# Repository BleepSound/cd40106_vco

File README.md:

[![CC BY-SA 4.0][cc-by-sa-shield]][cc-by-sa]

# CD40106 VCO

Latest documentation available at https://bleepsound.github.io/modules/

[![CC BY-SA 4.0][cc-by-sa-image]][cc-by-sa]

[cc-by-sa]: http://creativecommons.org/licenses/by-sa/4.0/
[cc-by-sa-image]: https://licensebuttons.net/l/by-sa/4.0/88x31.png
[cc-by-sa-shield]: https://img.shields.io/badge/License-CC%20BY--SA%204.0-lightgrey.svg

[![CC BY-SA 4.0][cc-by-sa-shield]][cc-by-sa]

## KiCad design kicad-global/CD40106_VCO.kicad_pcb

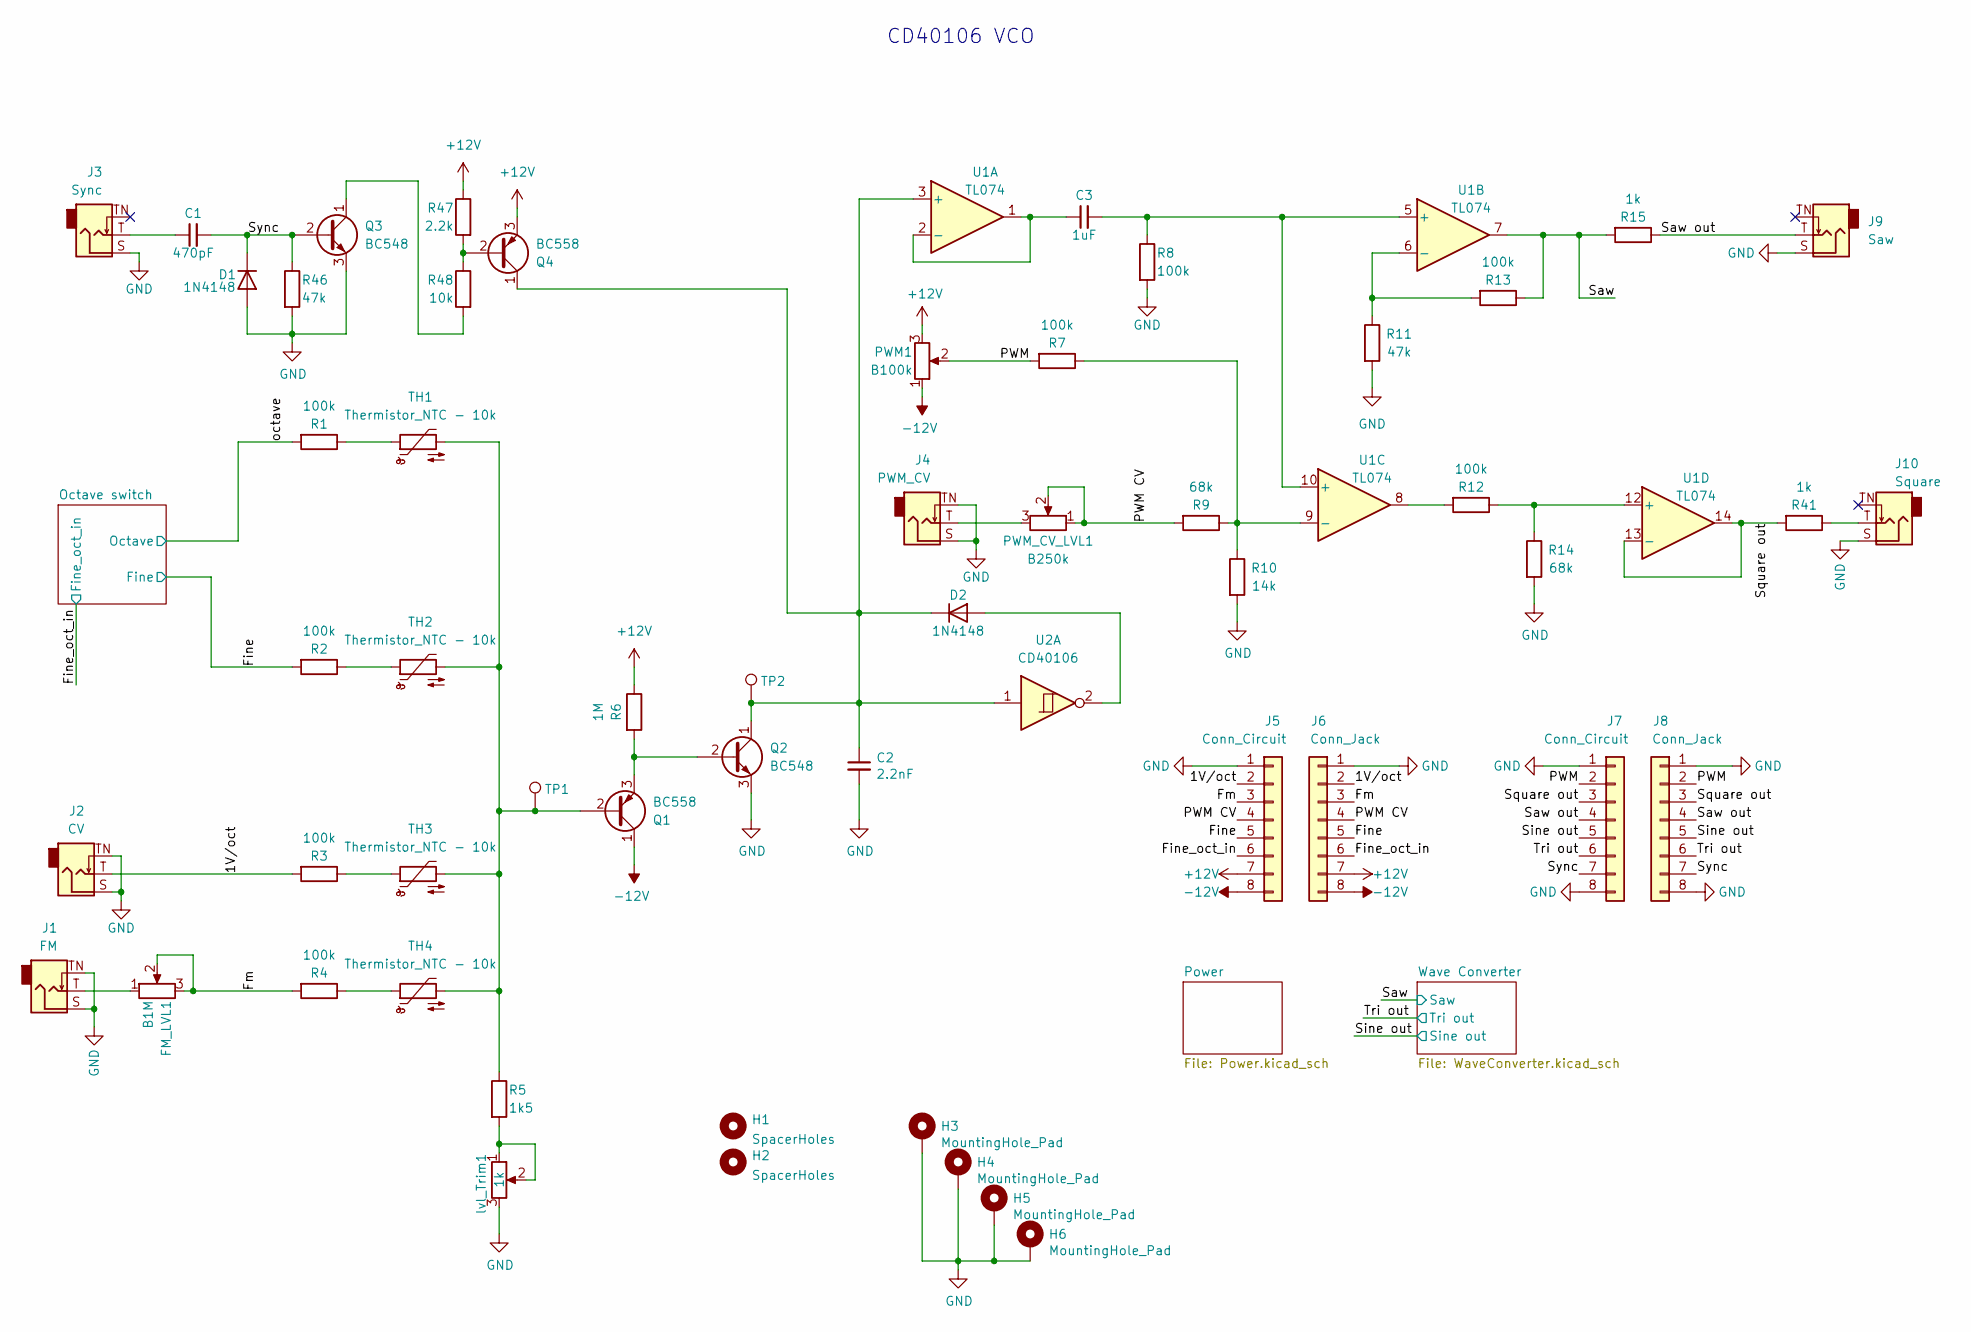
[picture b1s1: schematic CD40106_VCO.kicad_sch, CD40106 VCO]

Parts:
C1: 470pF; C_Disc_D7.0mm_W2.5mm_P5.00mm
C2: 2.2nF; C_Rect_L7.0mm_W2.5mm_P5.00mm
C3: 1uF; C_Disc_D7.0mm_W2.5mm_P5.00mm
D1, D2: 1N4148; D_DO-35_SOD27_P7.62mm_Horizontal
FM_LVL1: B1M; Pot-bourns-alpha
H1, H2: SpacerHoles; MountingHole_3.2mm_M3
H3, H4, H5, H6: MountingHole_Pad; Doepfer Mounting hole
J1: FM; Thonkiconn
J2: CV; Thonkiconn
J3: Sync; Thonkiconn
J4: PWM_CV; Thonkiconn
J5, J7: Conn_Circuit; PinSocket_1x08_P2.54mm_Vertical
J6, J8: Conn_Jack; PinHeader_1x08_P2.54mm_Vertical
J9: Saw; Thonkiconn
J10: Square; Thonkiconn
PWM1: B100k; Pot-bourns-alpha
PWM_CV_LVL1: B250k; Pot-bourns-alpha
Q1, Q4: BC558; TO-92_Inline
Q2, Q3: BC548; TO-92_Inline
R1, R2, R3, R4, R7, R8, R12, R13: 100k; R_Axial_DIN0207_L6.3mm_D2.5mm_P10.16mm_Horizontal
R5: 1k5; R_Axial_DIN0207_L6.3mm_D2.5mm_P10.16mm_Horizontal
R6: 1M; R_Axial_DIN0207_L6.3mm_D2.5mm_P10.16mm_Horizontal
R9, R14: 68k; R_Axial_DIN0207_L6.3mm_D2.5mm_P10.16mm_Horizontal
R10: 14k; R_Axial_DIN0207_L6.3mm_D2.5mm_P10.16mm_Horizontal
R11, R46: 47k; R_Axial_DIN0207_L6.3mm_D2.5mm_P10.16mm_Horizontal
R15, R41: 1k; R_Axial_DIN0207_L6.3mm_D2.5mm_P10.16mm_Horizontal
R47: 2.2k; R_Axial_DIN0207_L6.3mm_D2.5mm_P10.16mm_Horizontal
R48: 10k; R_Axial_DIN0207_L6.3mm_D2.5mm_P10.16mm_Horizontal
TH1, TH2, TH3, TH4: Thermistor_NTC - 10k; Therm_Disc_D6.5mm_W2.5mm_P3.50mm
TP1, TP2: TestPoint; TestPoint_Plated_Hole_D2.0mm
U1: TL074; DIP-14_W7.62mm_Socket
U2: CD40106; DIP-14_W7.62mm_LongPads
lvl_Trim1: 1k; Potentiometer_Bourns_3296W_Vertical

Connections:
+12V: J5.7, J6.7, PWM1.3, Q4.3 (E), R6.1, R47.1; also elsewhere on the board
-12V: J5.8, J6.8, PWM1.1, Q1.1 (C); also elsewhere on the board
/1V/oct: J2.T, J5.2, J6.2, R3.2
/Fine: J5.5, J6.5, R2.2; also elsewhere on the board
/Fine_oct_in: J5.6, J6.6; also elsewhere on the board
/Fm: FM_LVL1.2, FM_LVL1.3, J5.3, J6.3, R4.2
/PWM: J7.2, J8.2, PWM1.2, R7.2
/PWM CV: J5.4, J6.4, PWM_CV_LVL1.1, PWM_CV_LVL1.2, R9.2
/Saw: R13.1, R15.2, U1.7; also elsewhere on the board
/Saw out: J7.4, J8.4, J9.T, R15.1
/Sine out: J7.5, J8.5; also elsewhere on the board
/Square out: J7.3, J8.3, R41.2, U1.13 (-), U1.14
/Sync: C1.2, D1.1 (K), J7.7, J8.7, Q3.2 (B), R46.1
/Tri out: J7.6, J8.6; also elsewhere on the board
/octave: R1.2; also elsewhere on the board
GND: C2.2, D1.2 (A), H3.1, H4.1, H5.1, H6.1, J1.S, J1.TN, J2.S, J2.TN, J3.S, J4.S, J4.TN, J5.1, J6.1, J7.1, J7.8, J8.1, J8.8, J9.S, J10.S, Q2.3 (E), Q3.3 (E), R8.2, R10.2, R11.2, R14.2, R46.2, lvl_Trim1.3; also elsewhere on the board
unnamed: C1.1, J3.T
unnamed: D2.2 (A), U2.2
unnamed: C2.1, D2.1 (K), Q2.1 (C), Q4.1 (C), TP2.1, U1.3 (+), U2.1
unnamed: FM_LVL1.1, J1.T
unnamed: J4.T, PWM_CV_LVL1.3
unnamed: J10.T, R41.1
unnamed: Q1.2 (B), R5.1, TH1.2, TH2.2, TH3.2, TH4.2, TP1.1
unnamed: Q1.3 (E), Q2.2 (B), R6.2
unnamed: Q3.1 (C), R48.2
unnamed: Q4.2 (B), R47.2, R48.1
unnamed: R1.1, TH1.1
unnamed: R2.1, TH2.1
unnamed: R3.1, TH3.1
unnamed: R4.1, TH4.1
unnamed: R5.2, lvl_Trim1.1, lvl_Trim1.2
unnamed: R12.2, U1.8
unnamed: C3.1, U1.1, U1.2 (-)
unnamed: C3.2, R8.1, U1.5 (+), U1.10 (+)
unnamed: R11.1, R13.2, U1.6 (-)
unnamed: R7.1, R9.1, R10.1, U1.9 (-)
unnamed: R12.1, R14.1, U1.12 (+)

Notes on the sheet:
CD40106 VCO

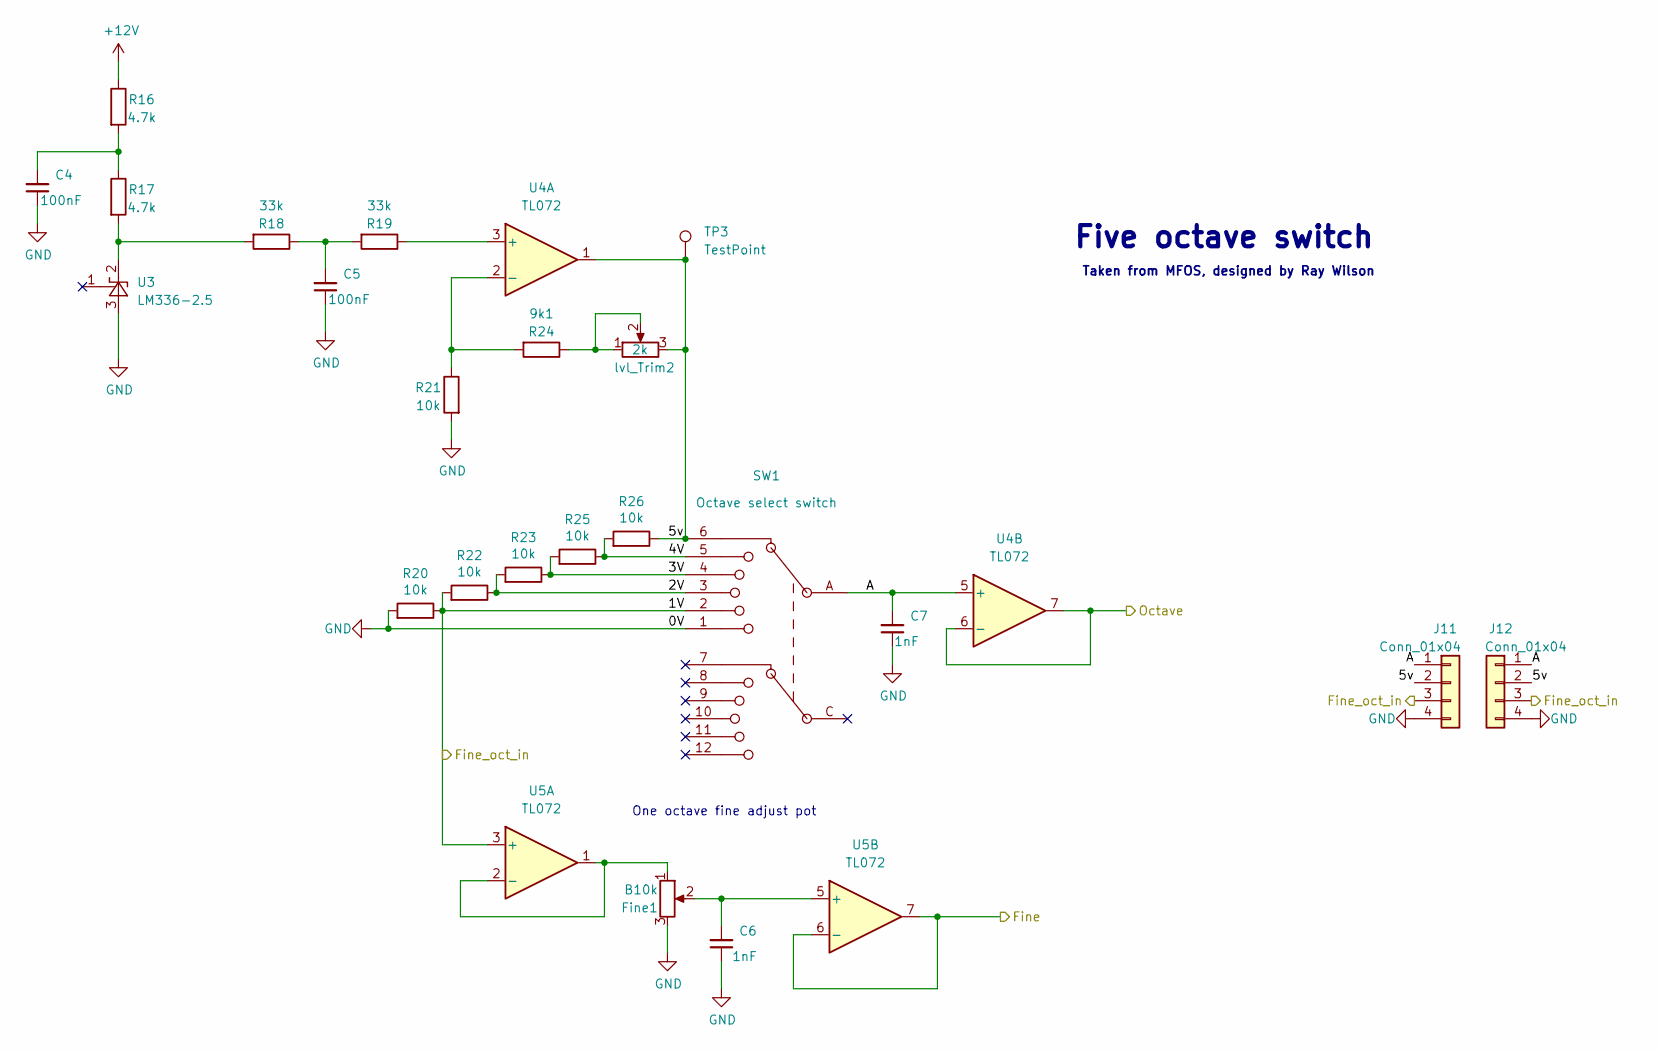
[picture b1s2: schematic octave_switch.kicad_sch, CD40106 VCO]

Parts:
C4, C5: 100nF; C_Disc_D7.0mm_W2.5mm_P5.00mm
C6, C7: 1nF; C_Disc_D7.0mm_W2.5mm_P5.00mm
Fine1: B10k; Pot-bourns-alpha
J11: Conn_01x04; PinHeader_1x04_P2.54mm_Vertical
J12: Conn_01x04; PinSocket_1x04_P2.54mm_Vertical
R16, R17: 4.7k; R_Axial_DIN0207_L6.3mm_D2.5mm_P10.16mm_Horizontal
R18, R19: 33k; R_Axial_DIN0207_L6.3mm_D2.5mm_P10.16mm_Horizontal
R20, R21, R22, R23, R25, R26: 10k; R_Axial_DIN0207_L6.3mm_D2.5mm_P10.16mm_Horizontal
R24: 9k1; R_Axial_DIN0207_L6.3mm_D2.5mm_P10.16mm_Horizontal
SW1: Octave select switch; CK1055
TP3: TestPoint; TestPoint_Plated_Hole_D2.0mm
U3: LM336-2.5; TO-92_Inline
U4, U5: TL072; DIP-8_W7.62mm_Socket
lvl_Trim2: 2k; Potentiometer_Bourns_3296W_Vertical

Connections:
+12V: R16.1; also elsewhere on the board
/Fine: U5.6 (-), U5.7; also elsewhere on the board
/Fine_oct_in: J11.3, J12.3, R20.1, R22.2, SW1.2, U5.3 (+); also elsewhere on the board
/Octave switch/2V: R22.1, R23.2, SW1.3
/Octave switch/3V: R23.1, R25.2, SW1.4
/Octave switch/4V: R25.1, R26.2, SW1.5
/Octave switch/5v: J11.2, J12.2, R26.1, SW1.6, TP3.1, U4.1, lvl_Trim2.3
/Octave switch/A: C7.2, J11.1, J12.1, SW1.A, U4.5 (+)
/octave: U4.6 (-), U4.7; also elsewhere on the board
GND: C4.1, C5.1, C6.1, C7.1, Fine1.3, J11.4, J12.4, R20.2, R21.2, SW1.1, U3.3 (A); also elsewhere on the board
unnamed: C4.2, R16.2, R17.1
unnamed: C5.2, R18.1, R19.2
unnamed: R24.1, lvl_Trim2.1, lvl_Trim2.2
unnamed: R17.2, R18.2, U3.2 (K)
unnamed: R19.1, U4.3 (+)
unnamed: R21.1, R24.2, U4.2 (-)
unnamed: Fine1.1, U5.1, U5.2 (-)
unnamed: C6.2, Fine1.2, U5.5 (+)

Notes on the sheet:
Five octave switch
Taken from MFOS, designed by Ray Wilson
One octave fine adjust pot

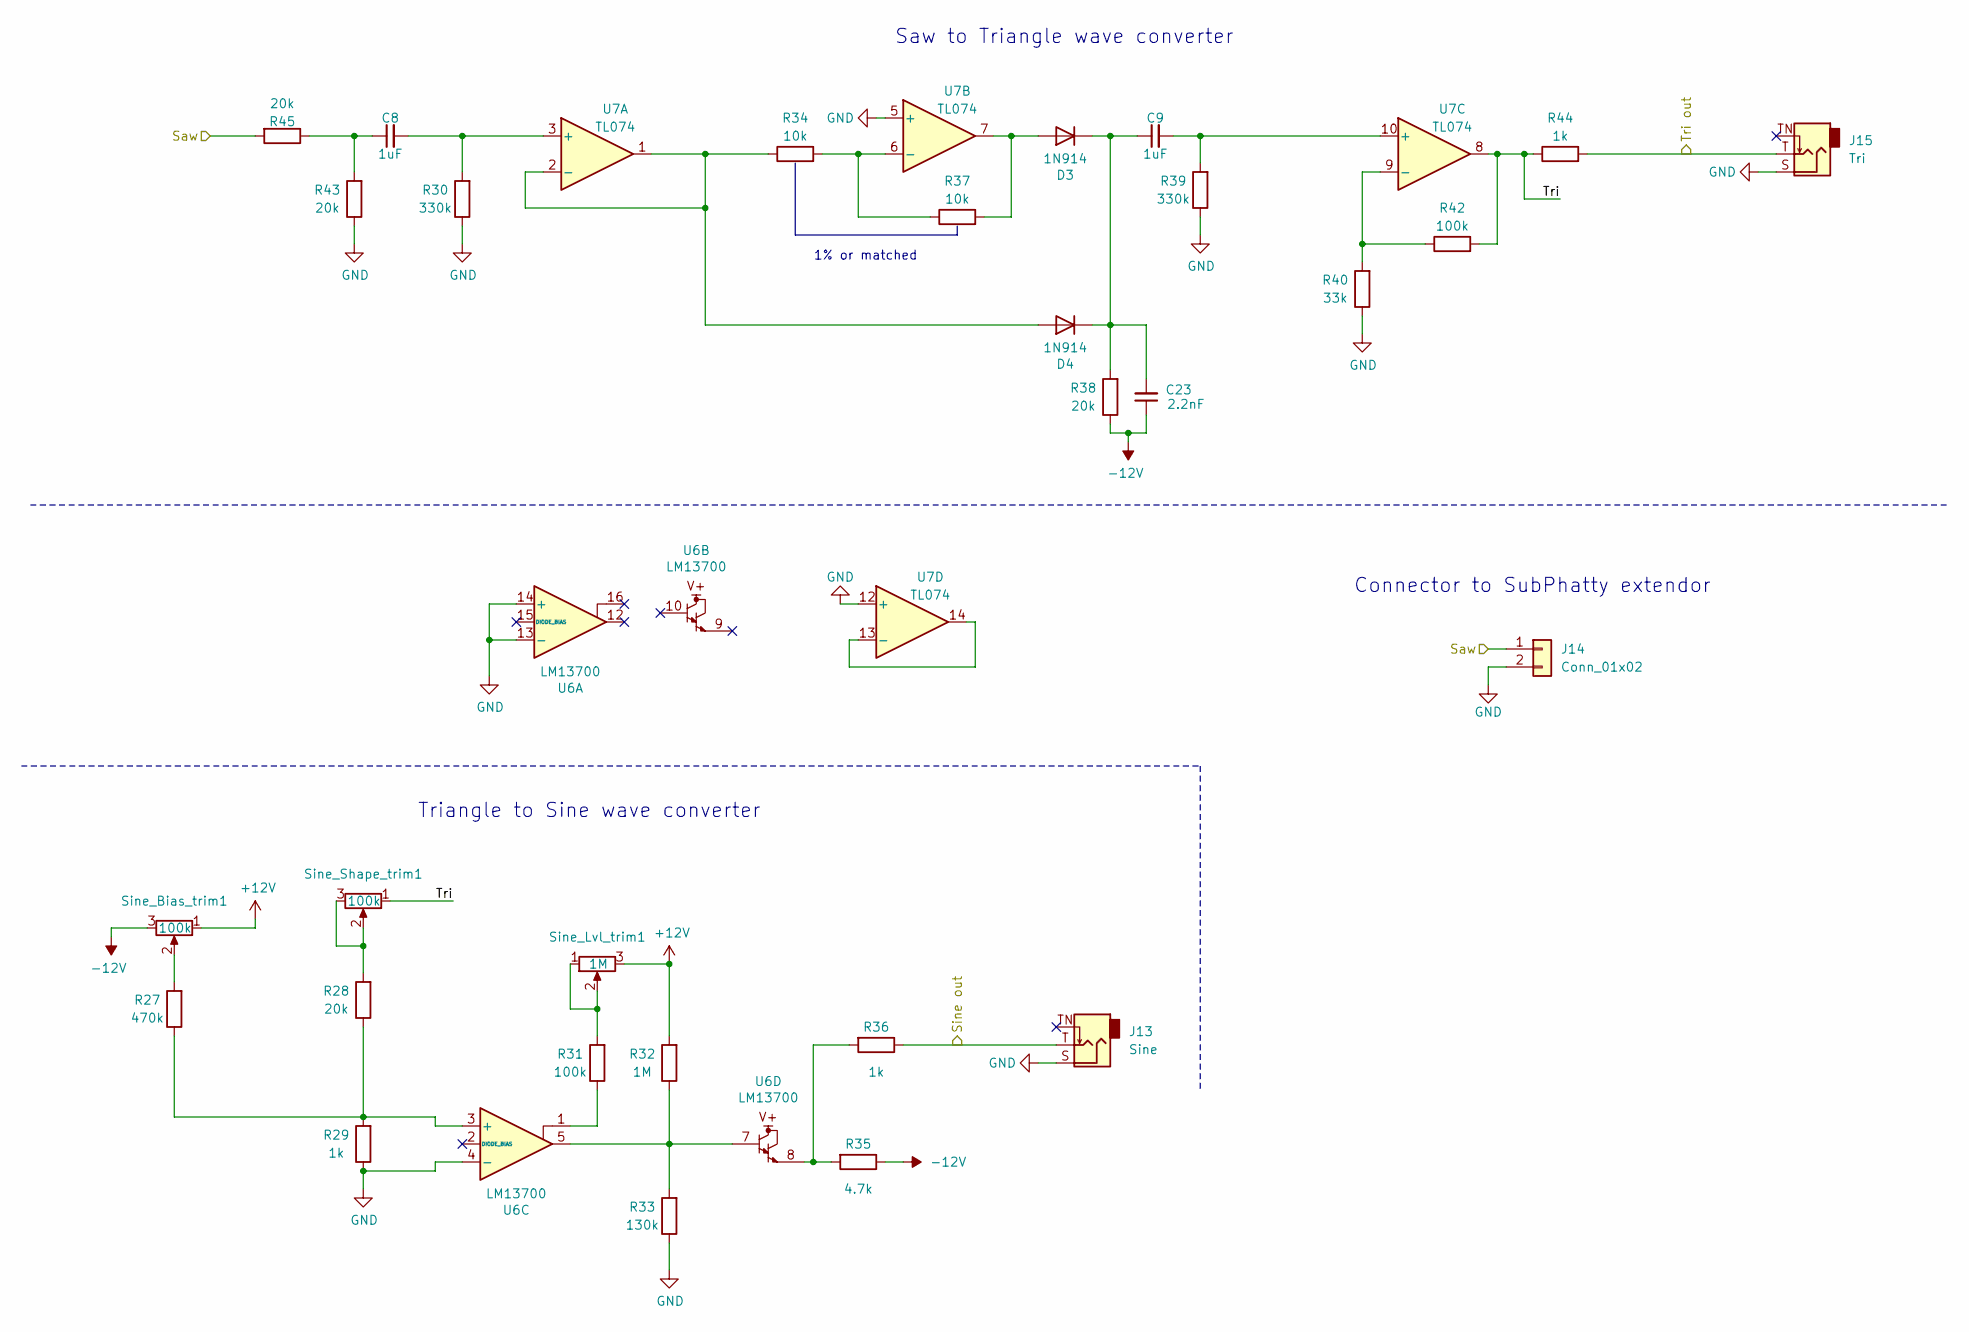
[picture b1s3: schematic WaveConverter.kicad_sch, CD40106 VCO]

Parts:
C8, C9: 1uF; C_Disc_D7.0mm_W2.5mm_P5.00mm
C23: 2.2nF; C_Disc_D7.0mm_W2.5mm_P5.00mm
D3, D4: 1N914; D_DO-35_SOD27_P7.62mm_Horizontal
J13: Sine; Thonkiconn
J14: Conn_01x02; PinHeader_1x02_P2.54mm_Vertical
J15: Tri; Thonkiconn
R27: 470k; R_Axial_DIN0207_L6.3mm_D2.5mm_P10.16mm_Horizontal
R28, R38, R43, R45: 20k; R_Axial_DIN0207_L6.3mm_D2.5mm_P10.16mm_Horizontal
R29, R36, R44: 1k; R_Axial_DIN0207_L6.3mm_D2.5mm_P10.16mm_Horizontal
R30, R39: 330k; R_Axial_DIN0207_L6.3mm_D2.5mm_P10.16mm_Horizontal
R31, R42: 100k; R_Axial_DIN0207_L6.3mm_D2.5mm_P10.16mm_Horizontal
R32: 1M; R_Axial_DIN0207_L6.3mm_D2.5mm_P10.16mm_Horizontal
R33: 130k; R_Axial_DIN0207_L6.3mm_D2.5mm_P10.16mm_Horizontal
R34, R37: 10k; R_Axial_DIN0207_L6.3mm_D2.5mm_P10.16mm_Horizontal
R35: 4.7k; R_Axial_DIN0207_L6.3mm_D2.5mm_P10.16mm_Horizontal
R40: 33k; R_Axial_DIN0207_L6.3mm_D2.5mm_P10.16mm_Horizontal
Sine_Bias_trim1: 100k; Potentiometer_Bourns_3296W_Vertical
Sine_Lvl_trim1: 1M; Potentiometer_Bourns_3296W_Vertical
Sine_Shape_trim1: 100k; Potentiometer_Bourns_3296W_Vertical
U6: LM13700; SOIC-16_3.9x9.9mm_P1.27mm
U7: TL074; DIP-14_W7.62mm_Socket

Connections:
+12V: R32.2, Sine_Bias_trim1.1, Sine_Lvl_trim1.3; also elsewhere on the board
-12V: C23.1, R35.1, R38.1, Sine_Bias_trim1.3; also elsewhere on the board
/Saw: J14.1, R45.2; also elsewhere on the board
/Sine out: J13.T, R36.1; also elsewhere on the board
/Tri out: J15.T, R44.2; also elsewhere on the board
/Wave Converter/Tri: R42.2, R44.1, Sine_Shape_trim1.1, U7.8
GND: J13.S, J14.2, J15.S, R29.1, R30.1, R33.1, R39.1, R40.1, R43.1, U6.4 (-), U6.13 (-), U6.14 (+), U7.5 (+), U7.12 (+); also elsewhere on the board
unnamed: C8.1, R43.2, R45.1
unnamed: D3.2 (A), R37.2, U7.7
unnamed: C9.1, C23.2, D3.1 (K), D4.1 (K), R38.2
unnamed: D4.2 (A), R34.1, U7.1, U7.2 (-)
unnamed: R27.2, Sine_Bias_trim1.2
unnamed: R28.2, Sine_Shape_trim1.2, Sine_Shape_trim1.3
unnamed: R31.1, U6.1
unnamed: R31.2, Sine_Lvl_trim1.1, Sine_Lvl_trim1.2
unnamed: R32.1, R33.2, U6.5, U6.7
unnamed: R35.2, R36.2, U6.8
unnamed: R27.1, R28.1, R29.2, U6.3 (+)
unnamed: C8.2, R30.2, U7.3 (+)
unnamed: R34.2, R37.1, U7.6 (-)
unnamed: C9.2, R39.2, U7.10 (+)
unnamed: R40.2, R42.1, U7.9 (-)
unnamed: U7.13 (-), U7.14

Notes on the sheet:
Saw to Triangle wave converter
Triangle to Sine wave converter
1% or matched
Connector to SubPhatty extendor

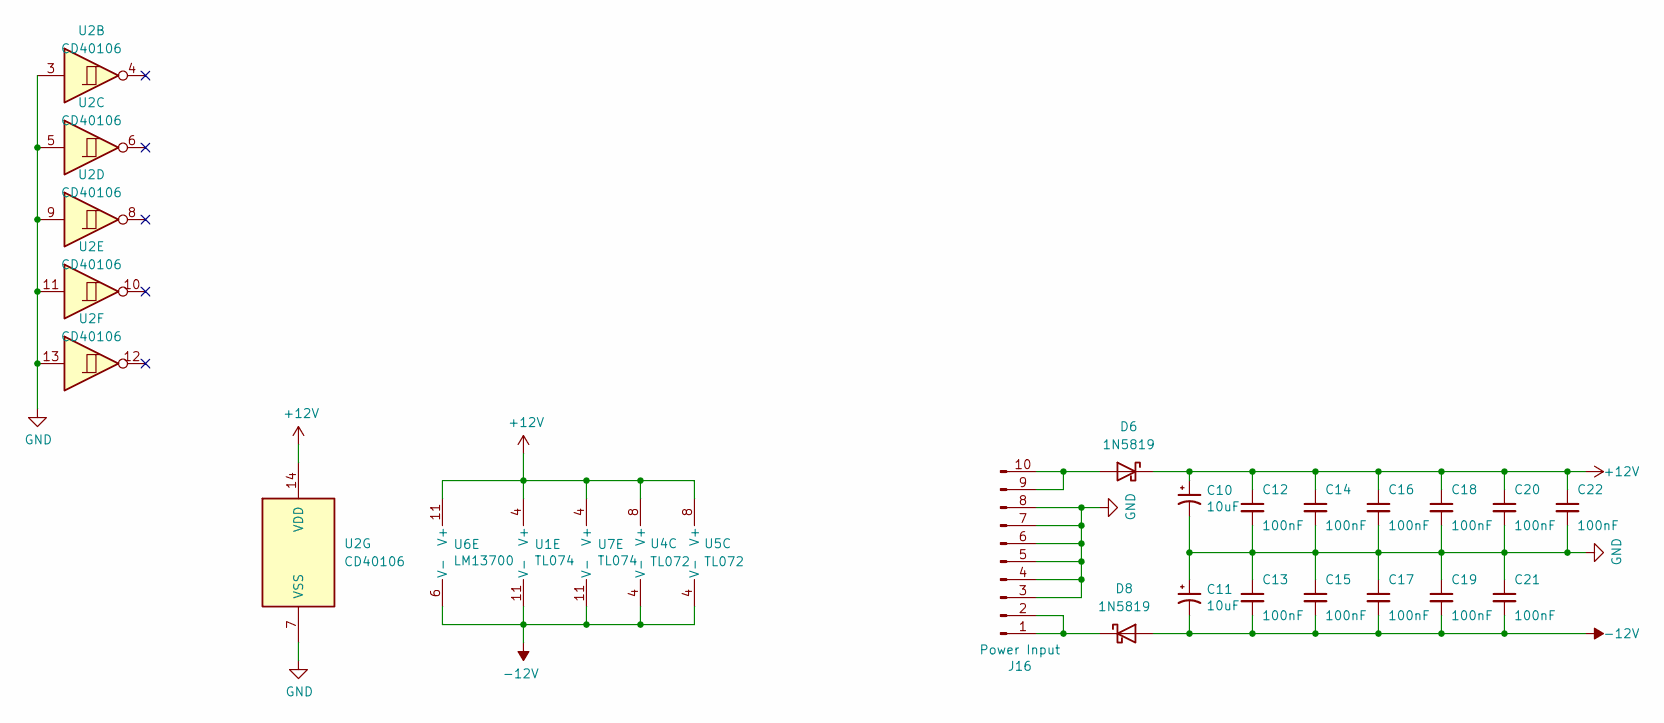
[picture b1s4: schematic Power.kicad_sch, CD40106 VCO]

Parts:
C10, C11: 10uF; CP_Radial_D5.0mm_P2.00mm
C12, C13, C14, C15, C16, C17, C18, C19, C20, C21, C22: 100nF; C_Disc_D7.0mm_W2.5mm_P5.00mm
D6, D8: 1N5819; D_DO-41_SOD81_P10.16mm_Horizontal
J16: Power Input; IDC-Header_2x05_P2.54mm_Vertical
U1, U7: TL074; DIP-14_W7.62mm_Socket
U2: CD40106; DIP-14_W7.62mm_LongPads
U4, U5: TL072; DIP-8_W7.62mm_Socket
U6: LM13700; SOIC-16_3.9x9.9mm_P1.27mm

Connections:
+12V: C10.1, C12.1, C14.1, C16.1, C18.1, C20.1, C22.1, D6.1 (K), U1.4 (V+), U2.14 (VDD), U4.8 (V+), U5.8 (V+), U6.11 (V+), U7.4 (V+); also elsewhere on the board
-12V: C11.2, C13.2, C15.2, C17.2, C19.2, C21.2, D8.2 (A), U1.11 (V-), U4.4 (V-), U5.4 (V-), U6.6 (V-), U7.11 (V-); also elsewhere on the board
GND: C10.2, C11.1, C12.2, C13.1, C14.2, C15.1, C16.2, C17.1, C18.2, C19.1, C20.2, C21.1, C22.2, J16.3, J16.4, J16.5, J16.6, J16.7, J16.8, U2.3, U2.5, U2.7 (VSS), U2.9, U2.11, U2.13; also elsewhere on the board
unnamed: D6.2 (A), J16.9, J16.10
unnamed: D8.1 (K), J16.1, J16.2

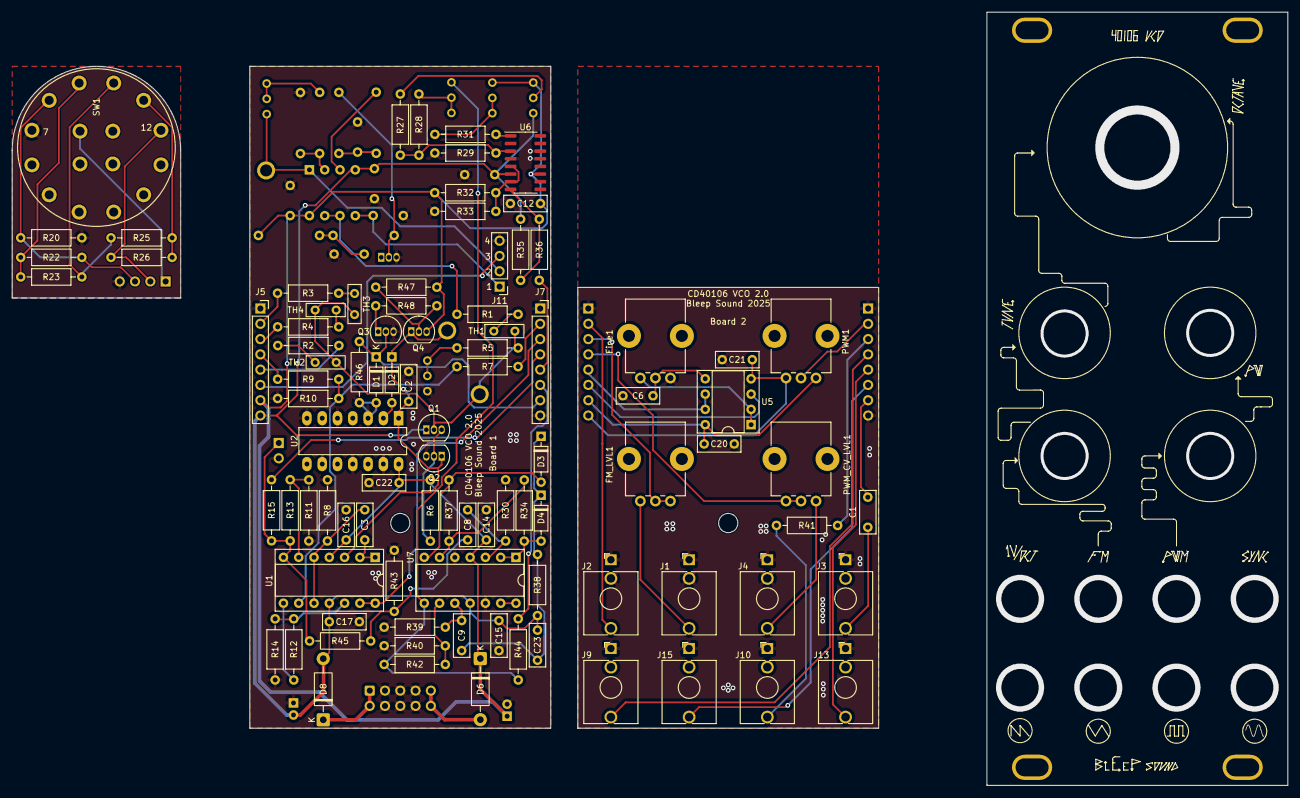
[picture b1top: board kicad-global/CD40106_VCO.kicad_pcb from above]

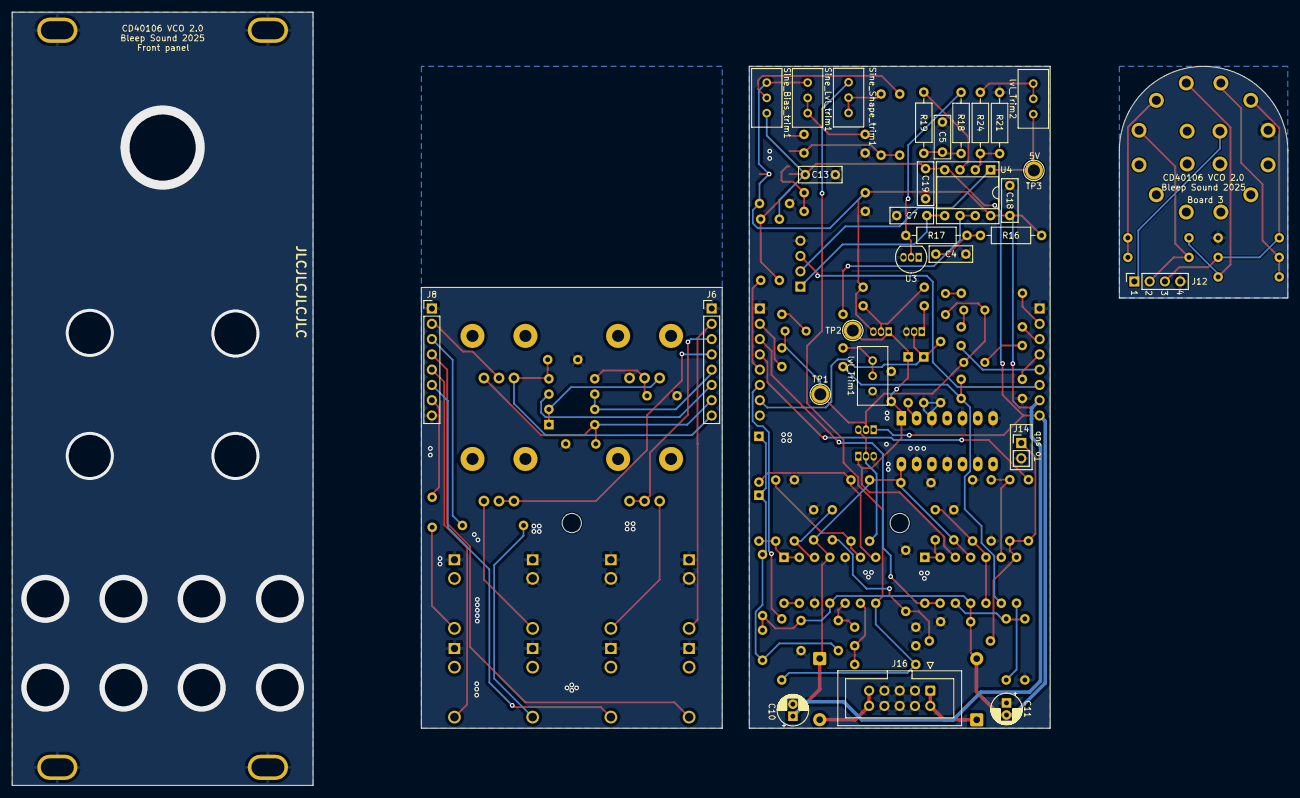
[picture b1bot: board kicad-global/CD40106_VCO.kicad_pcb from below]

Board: 2 copper layers, 212.0 x 128.5 mm, 127 parts (29 on the bottom side), 69 nets.

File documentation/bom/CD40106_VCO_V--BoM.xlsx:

CD40106_VCO_V Bill of Materials
Schematic: | CD40106_VCO | Component Groups: | 54
Variant: | default | Component Count: | 109 (1 SMD/ 107 THT)
Revision: |  | Fitted Components: | 109 (1 SMD/ 107 THT)
Date: | 2023-11-27_21-44-50 | Number of PCBs: | 1
KiCad Version: | 7.0.7-7.0.7~ubuntu22.04.1 | Total Components: | 109
Row | Description | References | Value | Quantity Per PCB | Comments
1 | Unpolarized capacitor, small symbol | C6 C7 | 1nF | 2
2 | Unpolarized capacitor, small symbol | C1 | 2.2nF | 1 | Mica capacitor for stability
3 | Unpolarized capacitor, small symbol | C4 C5 C12 C13 C14 C15 C16 C17 C18 C19 C20 C21 C22 | 100nF | 13
4 | Unpolarized capacitor, small symbol | C3 C8 C9 | 1uF | 3
5 |  | C10 C11 | 10uF | 2
6 | Unpolarized capacitor, small symbol | C2 | Optionnal | 1 | If you don't have a mica capacitor, just use a regular ceramic one
7 | Diode | D1 D2 | 1N4148 | 2
8 | Diode | D3 D4 | 1N914 | 2
9 |  | FB1 FB2 | 10R | 2 | Ferrite beads (or inductance)
10 |  | FM_LVL1 | 1M | 1
11 |  | Fine1 | 10k | 1
12 | Thonkiconn Audio Jack | J2 | CV | 1 | Thonkiconn jack
13 | Generic connector, single row, 01x02, script generated (kicad-library-utils/sch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 | J14 | Conn_01x02 | 1
14 | Generic connector, single row, 01x04, script generated (kicad-library-utils/sch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 | J11 | Conn_01x04 | 1
15 | Generic connector, single row, 01x04, script generated (kicad-library-utils/sch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 | J12 | Conn_01x04 | 1
16 | Generic connector, single row, 01x08, script generated (kicad-library-utils/sch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 | J5 J7 | Conn_Circuit | 2
17 | Generic connector, single row, 01x08, script generated (kicad-library-utils/sch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 | J6 J8 | Conn_Jack | 2
18 | Thonkiconn Audio Jack | J1 | FM | 1 | Thonkiconn jack
19 | Thonkiconn Audio Jack | J4 | PWM_CV | 1 | Thonkiconn jack
20 | Generic connector, single row, 01x10, script generated (kicad-library-utils/sch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 | J16 | Power Input | 1
21 | Thonkiconn Audio Jack | J9 | Saw | 1 | Thonkiconn jack
22 | Thonkiconn Audio Jack | J13 | Sine | 1 | Thonkiconn jack
23 | Thonkiconn Audio Jack | J10 | Square | 1 | Thonkiconn jack
24 | Thonkiconn Audio Jack | J3 | Sync | 1 | Thonkiconn jack
25 | Thonkiconn Audio Jack | J15 | Tri | 1 | Thonkiconn jack
26 |  | PWM1 | 100k | 1
27 |  | PWM_CV_LVL1 | 250k | 1
28 | 0.1A Ic, 30V Vce, Small Signal NPN Transistor, TO-92 | Q2 | BC548 | 1
29 | 0.1A Ic, 30V Vce, PNP Small Signal Transistor, TO-92 | Q1 | BC558 | 1
30 | Resistor | R15 R36 R44 | 1k | 3
31 | Resistor | R5 | 1k5 | 1
32 | Resistor | R16 R17 R35 | 4.7k | 3
33 | Resistor | R24 | 9k53 | 1
34 | Resistor | R20 R21 R22 R23 R25 R26 R34 R37 R40 R42 | 10k | 10
35 | Resistor | R10 | 14k | 1
36 | Resistor | R28 R29 R38 | 20k | 3
37 | Resistor | R18 R19 | 33k | 2
38 | Resistor | R11 | 47k | 1
39 | Resistor | R9 R14 | 68k | 2
40 | Resistor | R1 R2 R3 R4 R7 R8 R12 R31 | 100k | 8
41 | Resistor | R33 | 130k | 1
42 | Resistor | R30 R39 | 200k | 2
43 | Resistor | R27 | 470k | 1
44 | Resistor | R6 R13 R32 | 1M | 3
45 | 2 rotary switch with 6 positions | SW1 | Octave select switch | 1
46 |  | Sine_Bias_trim1 Sine_Shape_trim1 | 100k | 2 | Use multi turn Cermet style 3296 pots
47 |  | Sine_Lvl_trim1 | 1M | 1 | Use multi turn Cermet style 3296 pots
48 | Temperature dependent resistor, negative temperature coefficient | TH1 TH2 TH3 TH4 | Thermistor_NTC - 10k | 4
49 | Hex Schmitt trigger inverter | U2 | CD40106 | 1
50 | Dual Operational Transconductance Amplifiers with Linearizing Diodes and Buffer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 | U6 | LM13700 | 1
51 | Adjustable Micropower Voltage Reference Diodes, TO-92 | U3 | LM336BZ-5.0 | 1
52 | Dual Low-Noise JFET-Input Operational Amplifiers, DIP-8/SOIC-8 | U4 U5 | TL072 | 2
53 | Quad Low-Noise JFET-Input Operational Amplifiers, DIP-14/SOIC-14 | U1 U7 | TL074 | 2
54 |  | lvl_Trim1 lvl_Trim2 | 1k | 2 | Use multi turn Cermet style 3296 pots

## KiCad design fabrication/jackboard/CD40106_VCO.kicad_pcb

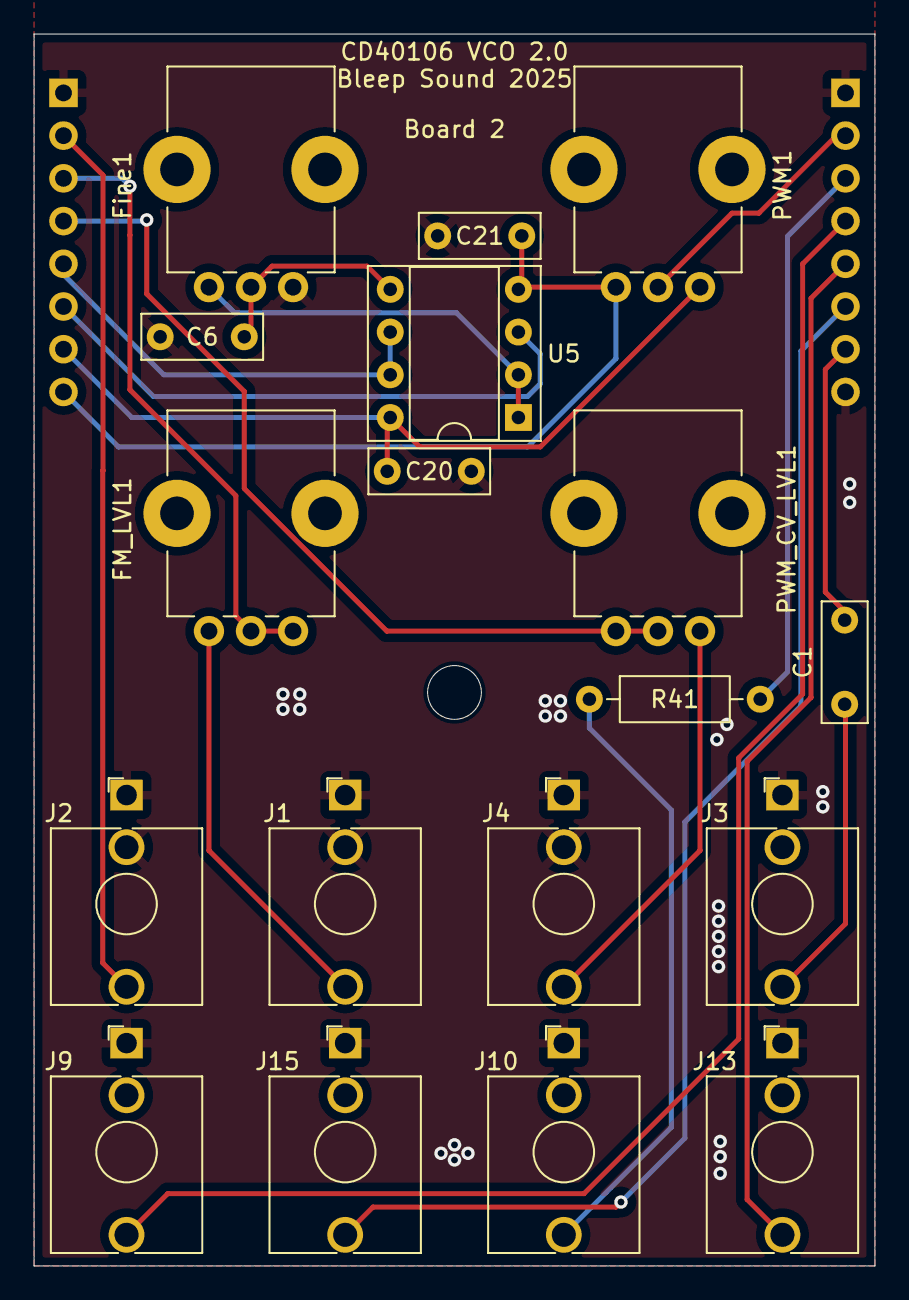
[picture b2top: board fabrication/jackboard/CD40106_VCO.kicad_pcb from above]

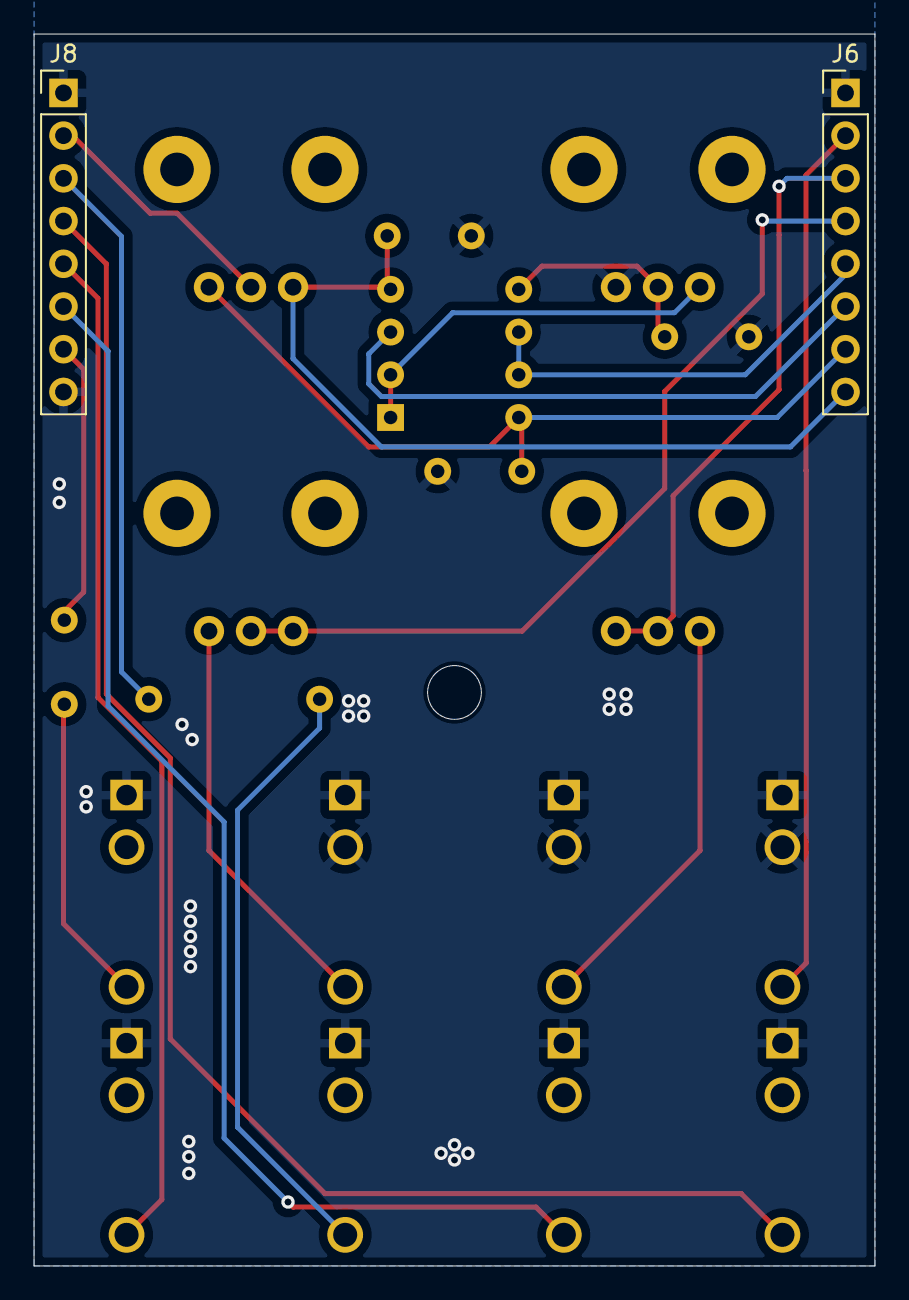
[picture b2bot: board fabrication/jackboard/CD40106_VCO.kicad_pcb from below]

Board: 2 copper layers, 50.0 x 73.2 mm, 21 parts (2 on the bottom side), 20 nets.

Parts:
C1: 470pF; C_Disc_D7.0mm_W2.5mm_P5.00mm
C6: 1nF; C_Disc_D7.0mm_W2.5mm_P5.00mm
C20, C21: 100nF; C_Disc_D7.0mm_W2.5mm_P5.00mm
FM_LVL1: B1M; Pot-bourns-alpha
Fine1: B10k; Pot-bourns-alpha
H1: SpacerHoles; MountingHole_3.2mm_M3
J1: FM; Thonkiconn
J2: CV; Thonkiconn
J3: Sync; Thonkiconn
J4: PWM_CV; Thonkiconn
J6, J8: Conn_Jack; PinHeader_1x08_P2.54mm_Vertical
J9: Saw; Thonkiconn
J10: Square; Thonkiconn
J13: Sine; Thonkiconn
J15: Tri; Thonkiconn
PWM1: B100k; Pot-bourns-alpha
PWM_CV_LVL1: B250k; Pot-bourns-alpha
R41: 1k; R_Axial_DIN0207_L6.3mm_D2.5mm_P10.16mm_Horizontal
U5: TL072; DIP-8_W7.62mm_Socket

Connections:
+12V: C20.1, J6.7, PWM1.3, U5.8 (V+)
-12V: C21.2, J6.8, PWM1.1, U5.4 (V-)
/1V/oct: J2.T, J6.2
/Fine: J6.5, U5.6 (-), U5.7
/Fine_oct_in: J6.6, U5.3 (+)
/Fm: FM_LVL1.2, FM_LVL1.3, J6.3
/PWM: J8.2, PWM1.2
/PWM CV: J6.4, PWM_CV_LVL1.1, PWM_CV_LVL1.2
/Saw out: J8.4, J9.T
/Sine out: J8.5, J13.T
/Square out: J8.3, R41.2
/Sync: C1.2, J8.7
/Tri out: J8.6, J15.T
GND: C6.1, C20.2, C21.1, Fine1.3, J1.S, J1.TN, J2.S, J2.TN, J3.S, J4.S, J4.TN, J6.1, J8.1, J8.8, J9.S, J10.S, J13.S, J15.S
unnamed: C1.1, J3.T
unnamed: FM_LVL1.1, J1.T
unnamed: J4.T, PWM_CV_LVL1.3
unnamed: J10.T, R41.1
unnamed: Fine1.1, U5.1, U5.2 (-)
unnamed: C6.2, Fine1.2, U5.5 (+)

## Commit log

2023-09-18 initial commit with data
2023-09-20 update components
2023-12-10 finished v1 of module
2023-12-10 add fab files
2023-12-10 doc + fab files for V1.0
2023-12-10 fix issues on readme
2023-12-10 fix bom link + extra info
2025-10-17 First proto fix
2025-10-19 V2.0
2025-10-19 Add link to website on readme
2025-11-27 add licence
